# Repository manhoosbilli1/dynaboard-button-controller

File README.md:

# DynaButton

Dynaboard - STM32F103 multi-button HID/control interface with USB-C and high-density I/O

## At a Glance

- **Status**: Routed
- **Board size**: 48.31 x 52.88 mm
- **Layers**: 4
- **Components**: 68
- **Key ICs**:
  - U1: STM32F103C8T6
  - U2: U_REG LD1117S50TR_SOT223
  - U3: AMS1117
  - U4: 74LVC2G241

## Schematic

Full PDF: [reports/schematic.pdf](reports/schematic.pdf)

## Component Roles

- **STM32F103C8T6** (U1) - main MCU (ARM Cortex-M3, 72 MHz); handles button matrix scanning and USB HID
- **74LVC2G241** (U4) - dual buffer/line driver for clean digital I/O signaling on the button outputs
- **LD1117S50TR** (U2) - 5 V LDO for peripheral rail
- **AMS1117** (U3) - 3.3 V LDO for the STM32 core
- **BSS138** x3 (Q1-Q3) - small-signal N-MOSFETs for level shifting / open-drain signaling between 3.3 V MCU and 5 V peripherals
- **X50328MSB2GI** - 8 MHz crystal for STM32 system clock
- **USB-Type-C 16-pin** connector for power + data
- **SS33 Schottky** x2 (D1, D3) - reverse-polarity protection / freewheel diodes
- **JST-PH 2 mm** connectors for daisy-chained external buttons (J_BTN5-J_BTN8) and pass-through I/O (J_IN2, J_OUT2)

## PCB

**Top copper**

**Bottom copper**

## Bill of Materials

| Refs | Value | Footprint | Qty | MPN | LCSC |
|------|-------|-----------|----:|-----|------|
| C1,C13 | 10uF | PCM_JLCPCB:C_0402 | 2 |  | [C15525](https://www.lcsc.com/product-detail/_C15525.html) |
| C2-C7,C9-C11,C14 | 100nF | PCM_JLCPCB:C_0402 | 10 |  | [C1525](https://www.lcsc.com/product-detail/_C1525.html) |
| C8,C12,C15 | 1uF | PCM_JLCPCB:C_0402 | 3 |  | [C52923](https://www.lcsc.com/product-detail/_C52923.html) |
| C17,C18 | 20pF | PCM_JLCPCB:C_0402 | 2 |  | [C1554](https://www.lcsc.com/product-detail/_C1554.html) |
| C19,C20 | 12pF | PCM_JLCPCB:C_0402 | 2 |  | [C1547](https://www.lcsc.com/product-detail/_C1547.html) |
| D1,D3 | SS33 | PCM_JLCPCB:D_SMA | 2 |  | [C28646294](https://www.lcsc.com/product-detail/_C28646294.html) |
| D2 | Red | PCM_JLCPCB:D_0603 | 1 |  | [C2286](https://www.lcsc.com/product-detail/_C2286.html) |
| D4 | Yellow | PCM_JLCPCB:D_0603 | 1 |  | [C89811](https://www.lcsc.com/product-detail/_C89811.html) |
| J3,J4 | Conn_02x03_Odd_Even | Connector_PinHeader_2.54mm:PinHeader_2x03_P2.54mm_Vertical | 2 |  |  |
| J5 | Connector, USB-TYPE-C-16P | PCM_JLCPCB:TYPE-C-SMD_HX-TYPE-C-16PIN | 1 |  | [C2927039](https://www.lcsc.com/product-detail/_C2927039.html) |
| J_BTN5-J_BTN8 | JST PH 2-pin 2mm | Connector_JST:JST_PH_S2B-PH-SM4-TB_1x02-1MP_P2.00mm_Horizontal | 4 |  |  |
| J_IN2,J_OUT2 | JST PH 3-pin 2mm | Connector_JST:JST_PH_B3B-PH-SM4-TB_1x03-1MP_P2.00mm_Vertical | 2 |  |  |
| Q1-Q3 | BSS138 | PCM_JLCPCB:Q_SOT-23 | 3 |  | [C7420339](https://www.lcsc.com/product-detail/_C7420339.html) |
| R1,R9-R11,R16-R21 | 10kΩ | PCM_JLCPCB:R_0402 | 10 |  | [C25744](https://www.lcsc.com/product-detail/_C25744.html) |
| R2,R5 | 5.1kΩ | PCM_JLCPCB:R_0402 | 2 |  | [C25905](https://www.lcsc.com/product-detail/_C25905.html) |
| R3 | 1MΩ | PCM_JLCPCB:R_0402 | 1 |  | [C26083](https://www.lcsc.com/product-detail/_C26083.html) |
| R4,R22 | 330Ω | PCM_JLCPCB:R_0402 | 2 |  | [C25104](https://www.lcsc.com/product-detail/_C25104.html) |
| R6,R7 | 100kΩ | PCM_JLCPCB:R_0402 | 2 |  | [C25741](https://www.lcsc.com/product-detail/_C25741.html) |
| R8,R23 | 20Ω | PCM_JLCPCB:R_0603 | 2 |  | [C22950](https://www.lcsc.com/product-detail/_C22950.html) |
| R14 | 4.7kΩ | PCM_JLCPCB:R_0402 | 1 |  | [C25900](https://www.lcsc.com/product-detail/_C25900.html) |
| S1 | Tactile Button, 160gf | PCM_JLCPCB:SW_TS-1088-AR02016 | 1 |  | [C720477](https://www.lcsc.com/product-detail/_C720477.html) |
| U1 | STM32F103C8T6 | PCM_JLCPCB:LQFP-48_7x7mm_P0.5mm | 1 |  | [C8734](https://www.lcsc.com/product-detail/_C8734.html) |
| U2 | U_REG LD1117S50TR_SOT223 | Package_TO_SOT_SMD:SOT-223-3_TabPin2 | 1 |  |  |
| U3 | AMS1117 | PCM_JLCPCB:SOT-223-3_L6.5-W3.4-P2.30-LS7.0-BR | 1 |  | [C6186](https://www.lcsc.com/product-detail/_C6186.html) |
| U4 | 74LVC2G241 | Package_SO:VSSOP-8_3x3mm_P0.65mm | 1 |  |  |
| X2 | X50328MSB2GI | PCM_JLCPCB:CRYSTAL-SMD_L5.0-W3.2 | 1 |  | [C115962](https://www.lcsc.com/product-detail/_C115962.html) |
| X3 | Q13FC1350000400 | PCM_JLCPCB:FC-135R_L3.2-W1.5 | 1 |  | [C32346](https://www.lcsc.com/product-detail/_C32346.html) |

_5 of 27 line items don't have an LCSC code in the schematic - search [LCSC](https://www.lcsc.com/) or [JLC parts search](https://jlcsearch.tscircuit.com/) by MPN or footprint when sourcing._

## Files

- `DynaButton.kicad_pro` - KiCad project
- `DynaButton.kicad_sch` - schematic source
- `DynaButton.kicad_pcb` - PCB layout source
- `reports/schematic.pdf` - full schematic (printable)
- `reports/bom.csv` - bill of materials
- `reports/pcb-top.svg`, `reports/pcb-bottom.svg` - copper artwork
- `reports/board-stats.json` - KiCad-generated board statistics

---

_Renders and metadata auto-generated by `Backup-KiCadProject.ps1` using KiCad 10.0._

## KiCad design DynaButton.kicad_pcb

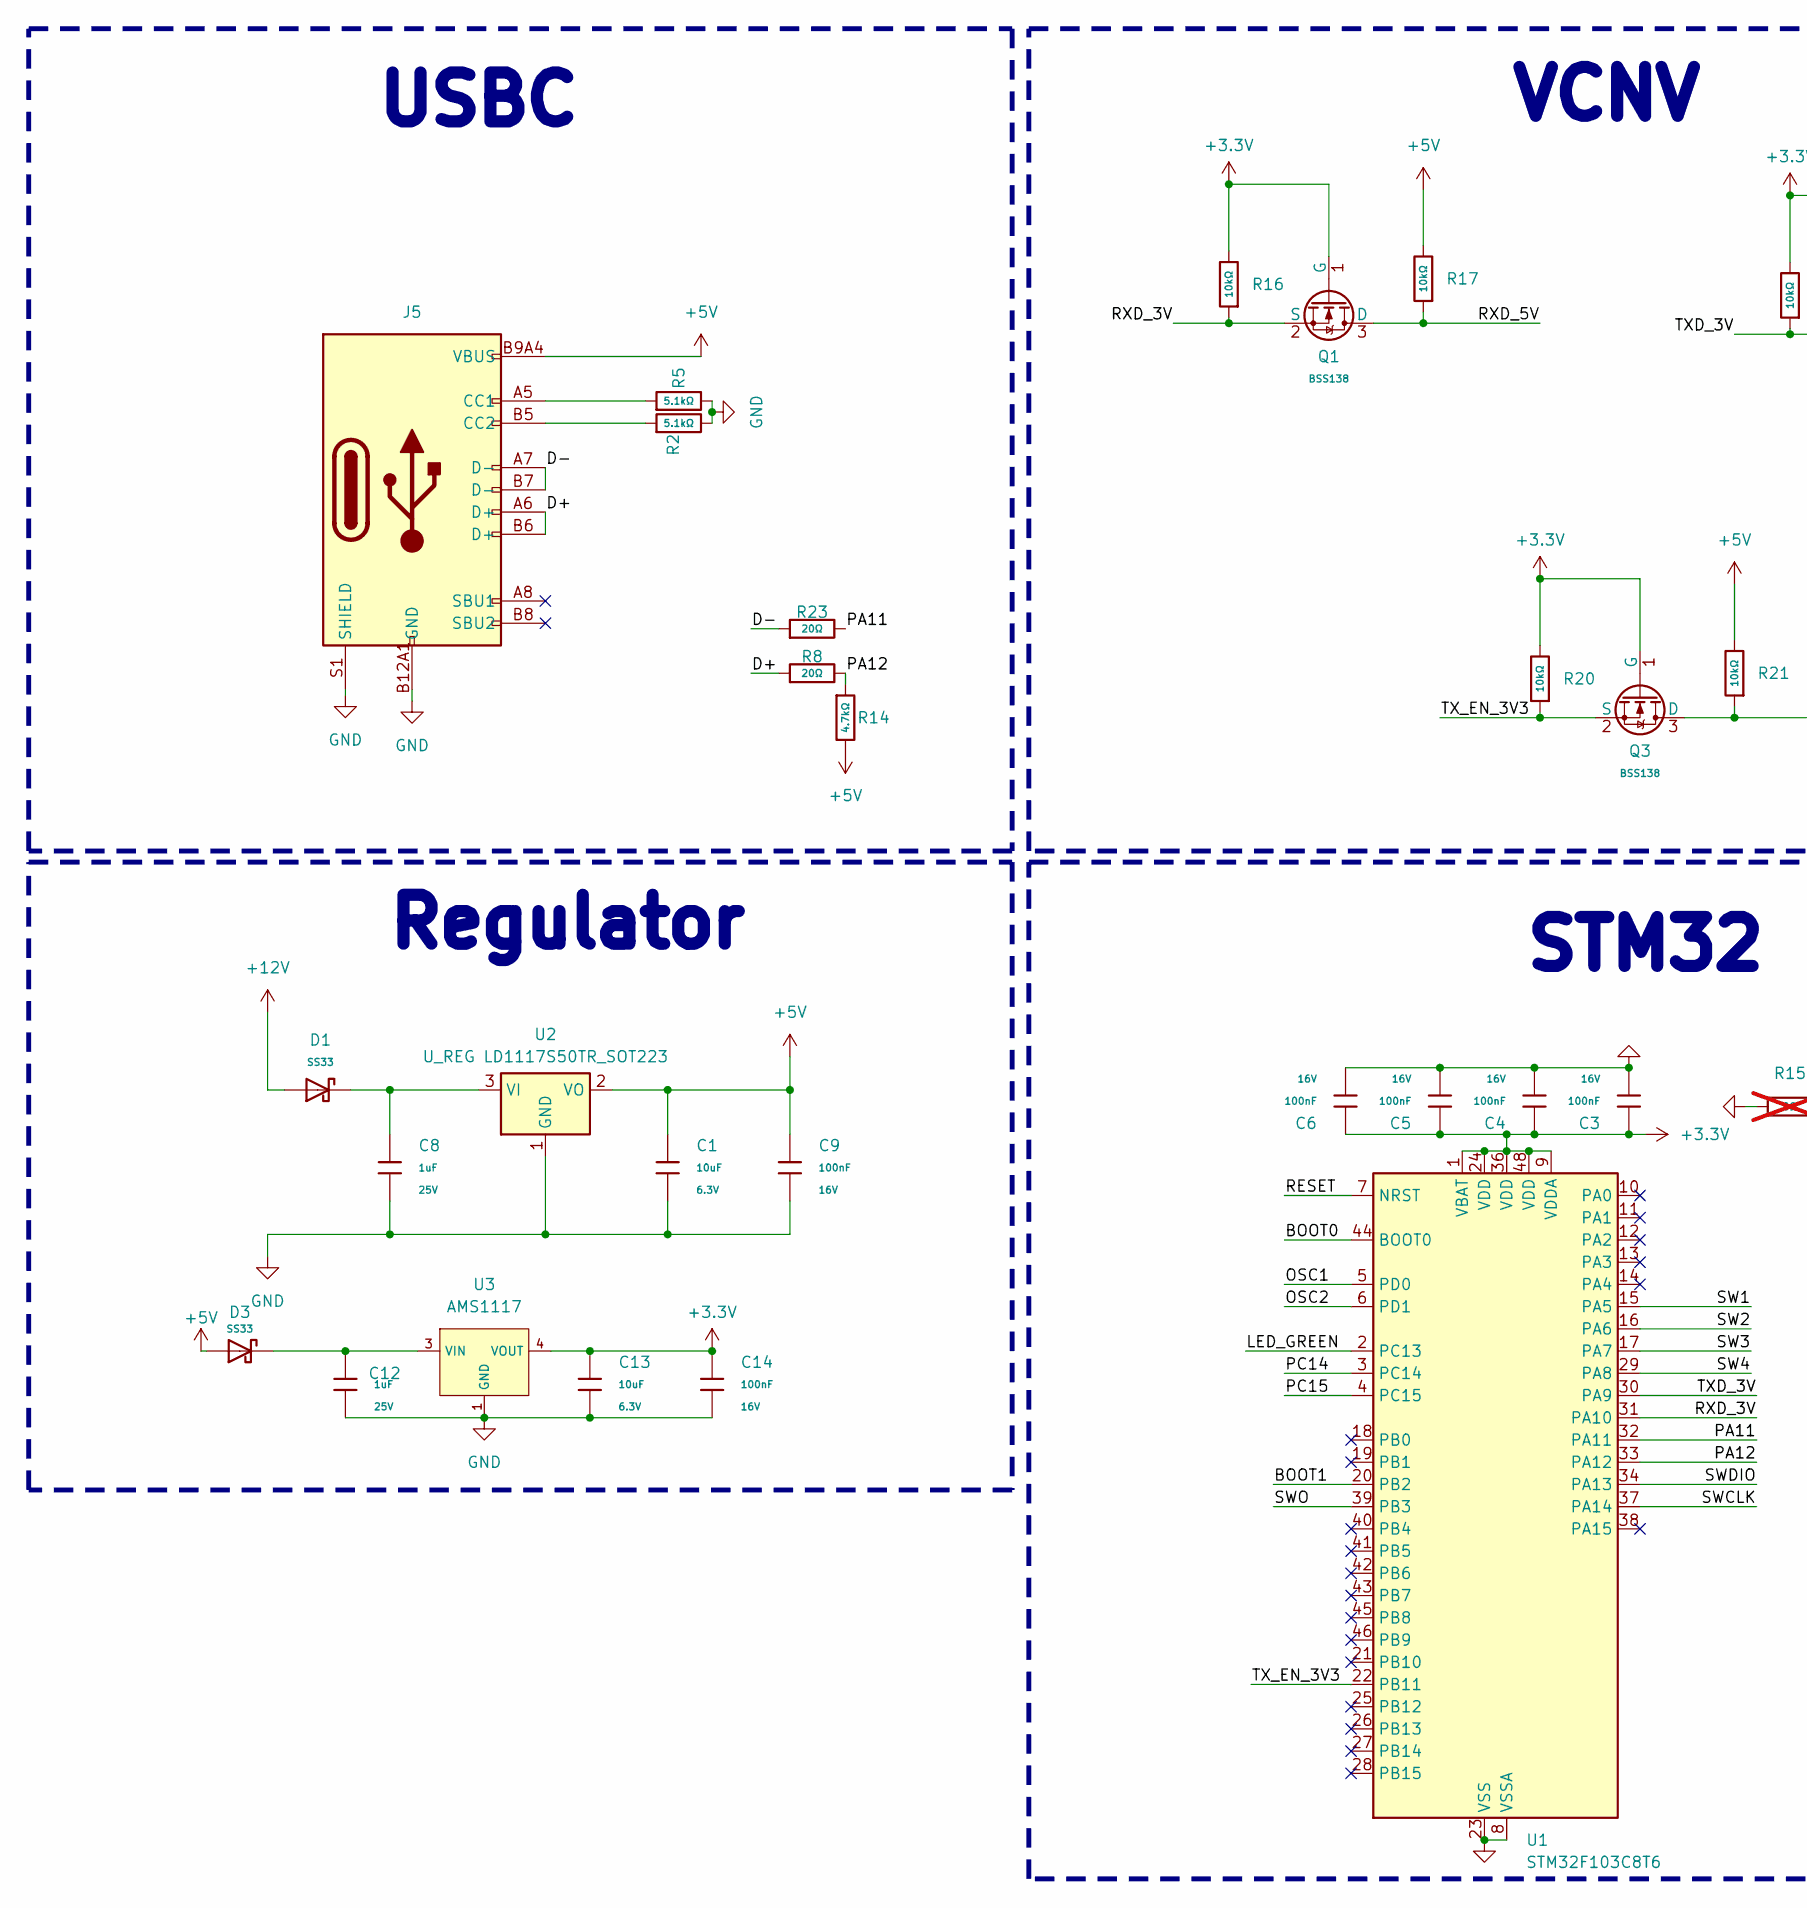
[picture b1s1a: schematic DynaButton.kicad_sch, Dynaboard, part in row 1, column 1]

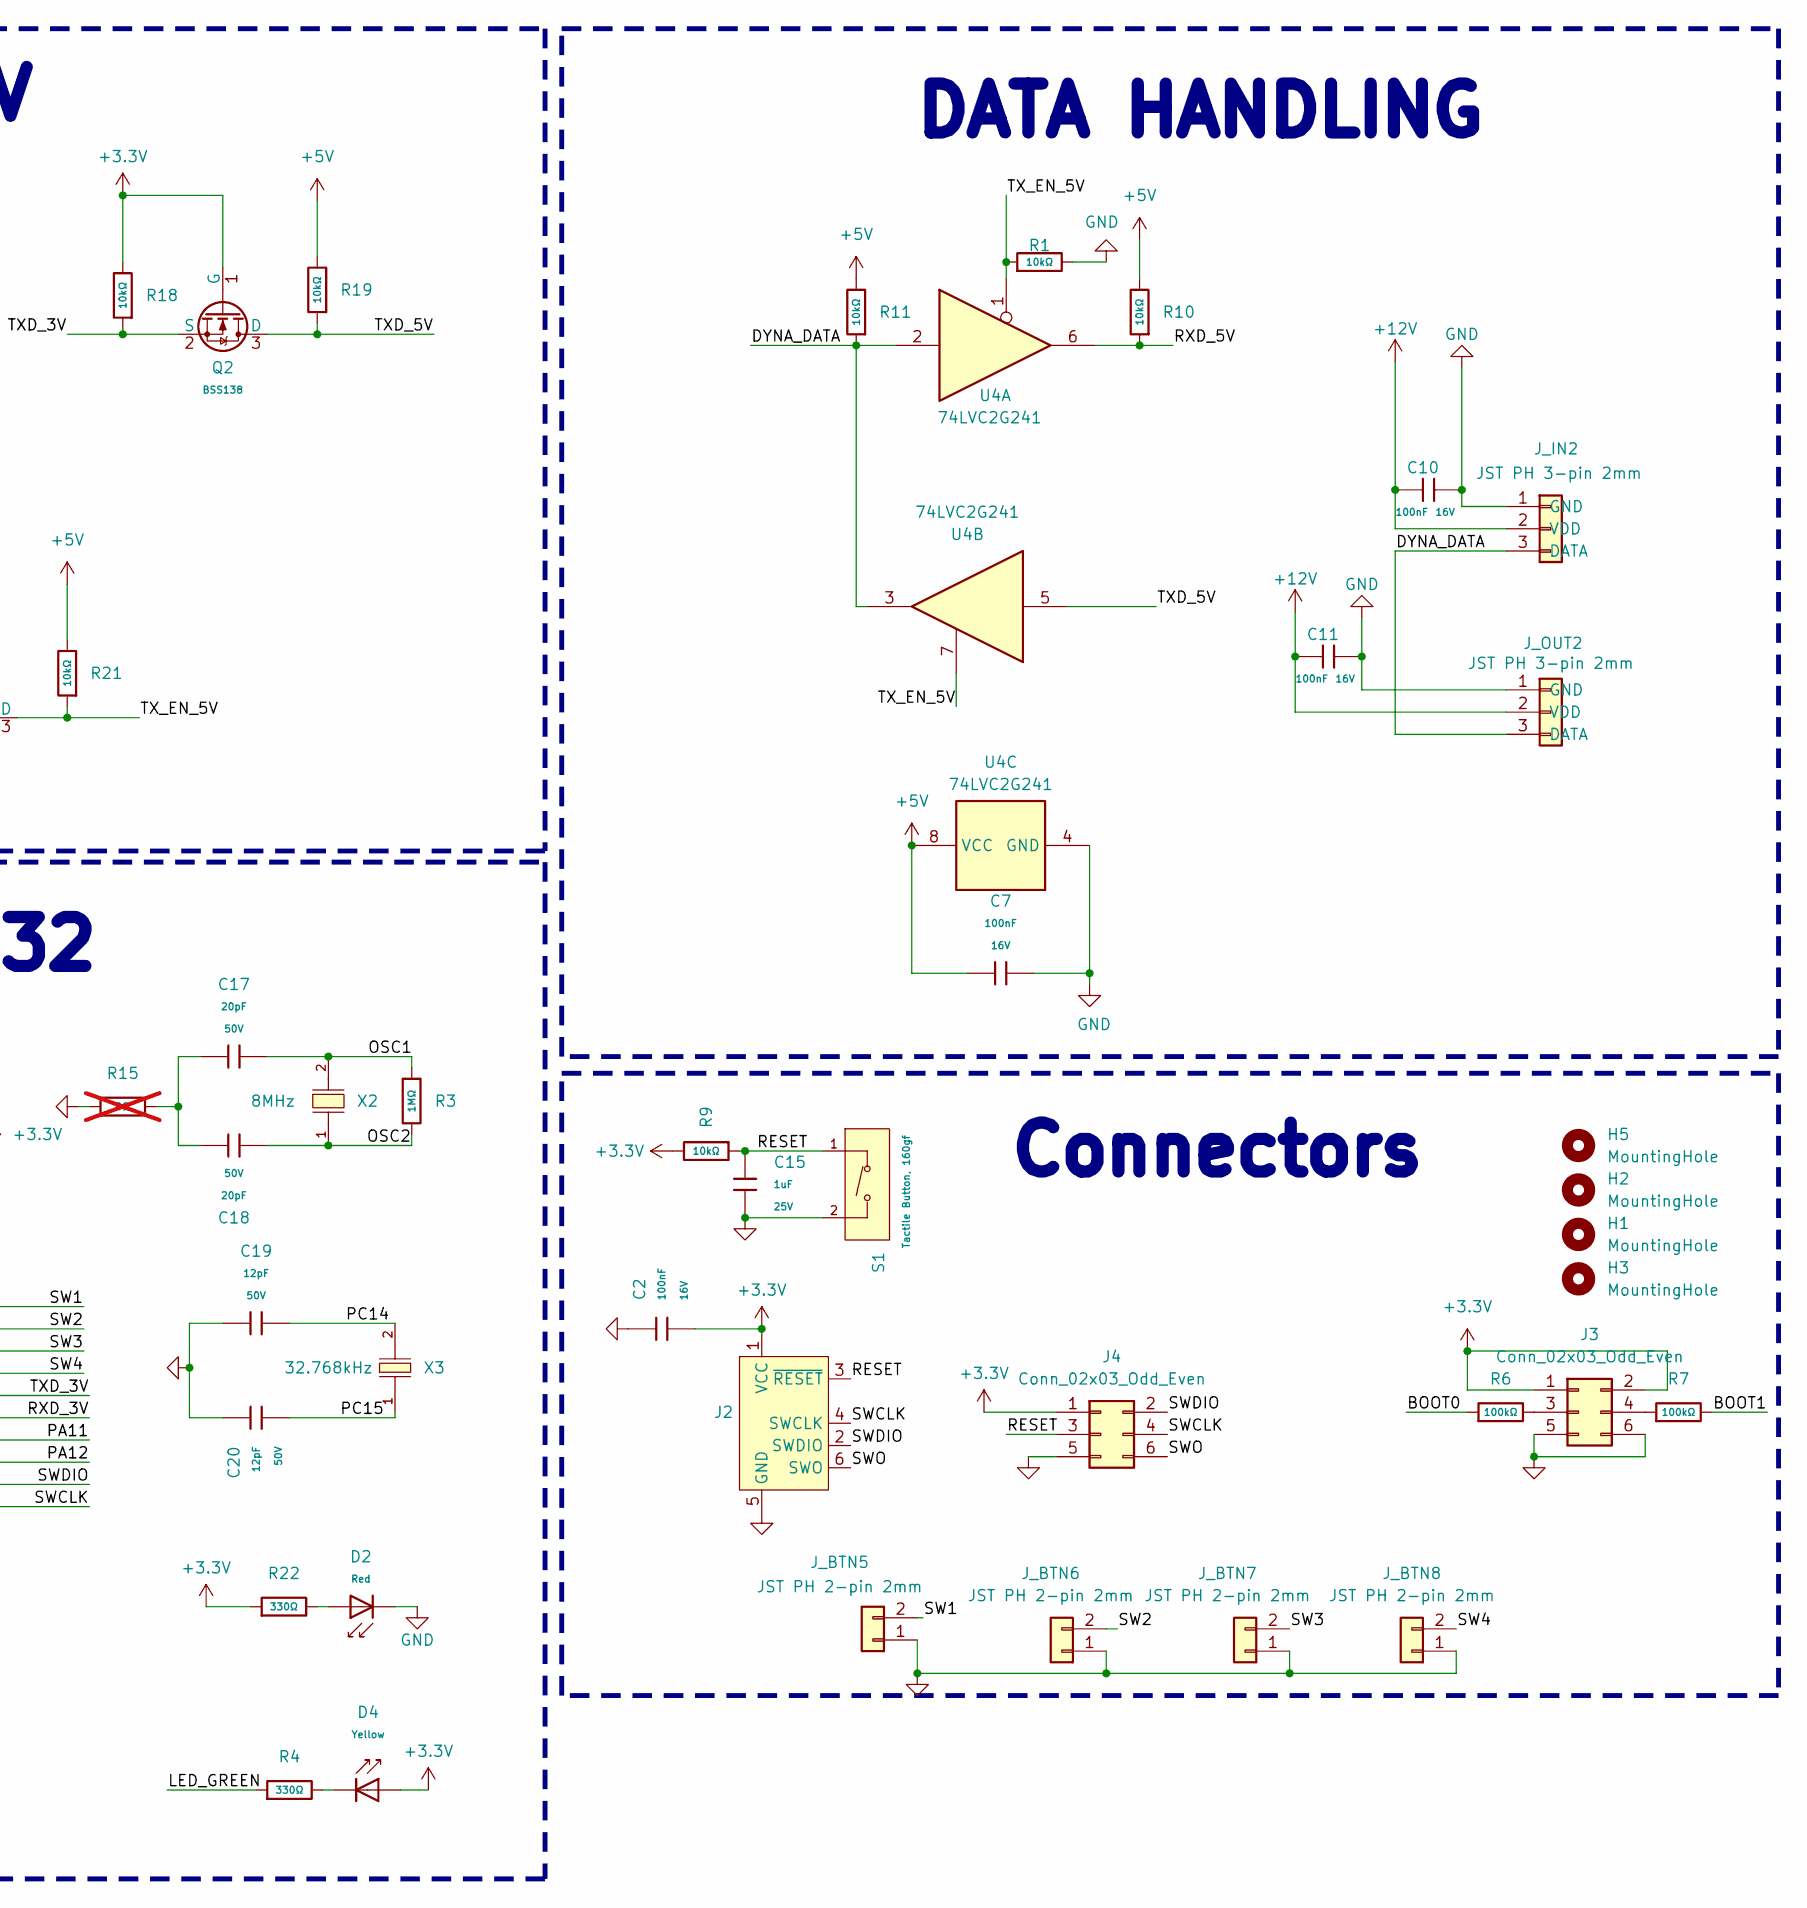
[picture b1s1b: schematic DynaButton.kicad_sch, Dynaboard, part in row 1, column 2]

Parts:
C1, C13: 10uF; C_0402; Voltage Rated 6.3V; Tolerance ±20%; Part CL05A106MQ5NUNC; LCSC C15525
C2, C3, C4, C5, C6, C7, C9, C10, C11, C14: 100nF; C_0402; Voltage Rated 16V; Tolerance ±10%; Part CL05B104KO5NNNC; LCSC C1525
C8, C12, C15: 1uF; C_0402; Voltage Rated 25V; Tolerance ±10%; Part CL05A105KA5NQNC; LCSC C52923
C17, C18: 20pF; C_0402; Voltage Rated 50V; Tolerance ±5%; Part 0402CG200J500NT; LCSC C1554
C19, C20: 12pF; C_0402; Voltage Rated 50V; Tolerance ±5%; Part 0402CG120J500NT; LCSC C1547
D1, D3: SS33; D_SMA; Part SS33; LCSC C28646294
D2: Red; D_0603; Part KT-0603R; LCSC C2286
D4: Yellow; D_0603; Forward Voltage (VF) 1.6V~2.6V; Part NCD0603Y2; LCSC C89811
H1, H2, H3, H5: MountingHole; MountingHole_2.2mm_M2
J2: Conn_ARM_SWD_TagConnect_TC2030; Tag-Connect_TC2030-IDC-FP_2x03_P1.27mm_Vertical
J3, J4: Conn_02x03_Odd_Even; PinHeader_2x03_P2.54mm_Vertical
J5: Connector, USB-TYPE-C-16P; TYPE-C-SMD_HX-TYPE-C-16PIN; LCSC C2927039
J_BTN5, J_BTN6, J_BTN7, J_BTN8: JST PH 2-pin 2mm; JST_PH_S2B-PH-SM4-TB_1x02-1MP_P2.00mm_Horizontal; PART NUMBER C295747
J_IN2: JST PH 3-pin 2mm; JST_PH_B3B-PH-SM4-TB_1x03-1MP_P2.00mm_Vertical; JLCPCB PART # C160353
J_OUT2: JST PH 3-pin 2mm; JST_PH_B3B-PH-SM4-TB_1x03-1MP_P2.00mm_Vertical; JLCPCB PART # C160353
Q1, Q2, Q3: BSS138; Q_SOT-23; Part BSS138; LCSC C7420339
R1, R9, R10, R11, R16, R17, R18, R19, R20, R21: 10kΩ; R_0402; Overload Voltage (Max) 50V; Tolerance ±1%; Part 0402WGF1002TCE; LCSC C25744
R2, R5: 5.1kΩ; R_0402; Overload Voltage (Max) 50V; Tolerance ±1%; Part 0402WGF5101TCE; LCSC C25905
R3: 1MΩ; R_0402; Overload Voltage (Max) 50V; Tolerance ±1%; Part 0402WGF1004TCE; LCSC C26083
R4, R22: 330Ω; R_0402; Overload Voltage (Max) 50V; Tolerance ±1%; Part 0402WGF3300TCE; LCSC C25104
R6, R7: 100kΩ; R_0402; Overload Voltage (Max) 50V; Tolerance ±1%; Part 0402WGF1003TCE; LCSC C25741
R8, R23: 20Ω; R_0603; Overload Voltage (Max) 75V; Tolerance ±1%; Part 0603WAF200JT5E; LCSC C22950
R14: 4.7kΩ; R_0402; Overload Voltage (Max) 50V; Tolerance ±1%; Part 0402WGF4701TCE; LCSC C25900
R15: 0Ω; R_0402; Overload Voltage (Max) 50V; Tolerance ±1%; Part 0402WGF0000TCE; LCSC C17168; not fitted
S1: Tactile Button, 160gf; SW_TS-1088-AR02016; Voltage Rating (Dc) 12V; Part TS-1088-AR02016; LCSC C720477
U1: STM32F103C8T6; LQFP-48_7x7mm_P0.5mm; Operating Voltage Range 2V~3.6V; Low Voltage Detection T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 2V~3.6V; Part STM32F103C8T6; LCSC C8734
U2: U_REG LD1117S50TR_SOT223; SOT-223-3_TabPin2; PART NUMBER C134077
U3: AMS1117; SOT-223-3_L6.5-W3.4-P2.30-LS7.0-BR; Output Voltage 3.3V; Dropout Voltage 1.3V@(800mA); Part AMS1117-3.3; LCSC C6186
U4: 74LVC2G241; VSSOP-8_3x3mm_P0.65mm
X2: X50328MSB2GI; CRYSTAL-SMD_L5.0-W3.2; Frequency Tolerance ±10ppm; Part X50328MSB2GI; LCSC C115962
X3: Q13FC1350000400; FC-135R_L3.2-W1.5; Frequency Tolerance ±20ppm; Part Q13FC13500004; LCSC C32346

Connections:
+3.3V: C2.2, C3.1, C4.1, C5.1, C6.1, C13.1, C14.1, D4.2, J2.1 (VCC), J3.1, J3.2, J4.1, Q1.1 (G), Q2.1 (G), Q3.1 (G), R9.2, R16.2, R18.2, R20.2, R22.1, U1.1 (VBAT), U1.9 (VDDA), U1.24 (VDD), U1.36 (VDD), U1.48 (VDD), U3.2 (VOUT), U3.4 (VOUT)
+5V: C1.1, C7.1, C9.1, D3.2, J5.A9B4 (VBUS), J5.B9A4 (VBUS), R10.2, R11.2, R14.2, R17.2, R19.2, R21.2, U2.2 (VO), U4.8 (VCC)
+12V: C10.2, C11.2, D1.2, J_IN2.2 (VDD), J_OUT2.2 (VDD)
/BOOT0: R6.1, U1.44 (BOOT0)
/BOOT1: R7.2, U1.20 (PB2)
/D+: J5.A6 (D+), J5.B6 (D+), R8.1
/D-: J5.A7 (D-), J5.B7 (D-), R23.1
/DYNA_DATA: J_IN2.3 (DATA), J_OUT2.3 (DATA), R11.1, U4.2, U4.3
/LED_GREEN: R4.1, U1.2 (PC13)
/OSC1: C17.2, R3.1, U1.5 (PD0), X2.2
/OSC2: C18.2, R3.2, U1.6 (PD1), X2.1
/PA11: R23.2, U1.32 (PA11)
/PA12: R8.2, R14.1, U1.33 (PA12)
/PC14: C19.2, U1.3 (PC14), X3.2
/PC15: C20.1, U1.4 (PC15), X3.1
/RESET: C15.1, J2.3 (~RESET), J4.3, R9.1, S1.1 (A), U1.7 (NRST)
/RXD_3V: Q1.2 (S), R16.1, U1.31 (PA10)
/RXD_5V: Q1.3 (D), R10.1, R17.1, U4.6
/SW1: J_BTN5.2, U1.15 (PA5)
/SW2: J_BTN6.2, U1.16 (PA6)
/SW3: J_BTN7.2, U1.17 (PA7)
/SW4: J_BTN8.2, U1.29 (PA8)
/SWCLK: J2.4 (SWCLK), J4.4, U1.37 (PA14)
/SWDIO: J2.2 (SWDIO), J4.2, U1.34 (PA13)
/SWO: J2.6 (SWO), J4.6, U1.39 (PB3)
/TXD_3V: Q2.2 (S), R18.1, U1.30 (PA9)
/TXD_5V: Q2.3 (D), R19.1, U4.5
/TX_EN_3V3: Q3.2 (S), R20.1, U1.22 (PB11)
/TX_EN_5V: Q3.3 (D), R1.1, R21.1, U4.1, U4.7
GND: C1.2, C2.1, C3.2, C4.2, C5.2, C6.2, C7.2, C8.2, C9.2, C10.1, C11.1, C12.2, C13.2, C14.2, C15.2, C19.1, C20.2, D2.1, J2.5 (GND), J3.5, J3.6, J4.5, J5.A12B1 (GND), J5.B12A1 (GND), J5.S1 (SHIELD), J_BTN5.1, J_BTN6.1, J_BTN7.1, J_BTN8.1, J_IN2.1 (GND), J_OUT2.1 (GND), R1.2, R2.2, R5.2, R15.1, S1.2 (B), U1.8 (VSSA), U1.23 (VSS), U1.35 (VSS), U1.47 (VSS), U2.1 (GND), U3.1 (GND), U4.4 (GND)
unnamed: C17.1, C18.1, R15.2
unnamed: D2.2, R22.2
unnamed: D4.1, R4.2
unnamed: J3.3, R6.2
unnamed: J3.4, R7.1
unnamed: J5.A5 (CC1), R5.1
unnamed: J5.B5 (CC2), R2.1
unnamed: C8.1, D1.1, U2.3 (VI)
unnamed: C12.1, D3.1, U3.3 (VIN)

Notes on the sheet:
Regulator
DATA HANDLING
USBC
STM32
Connectors
VCNV

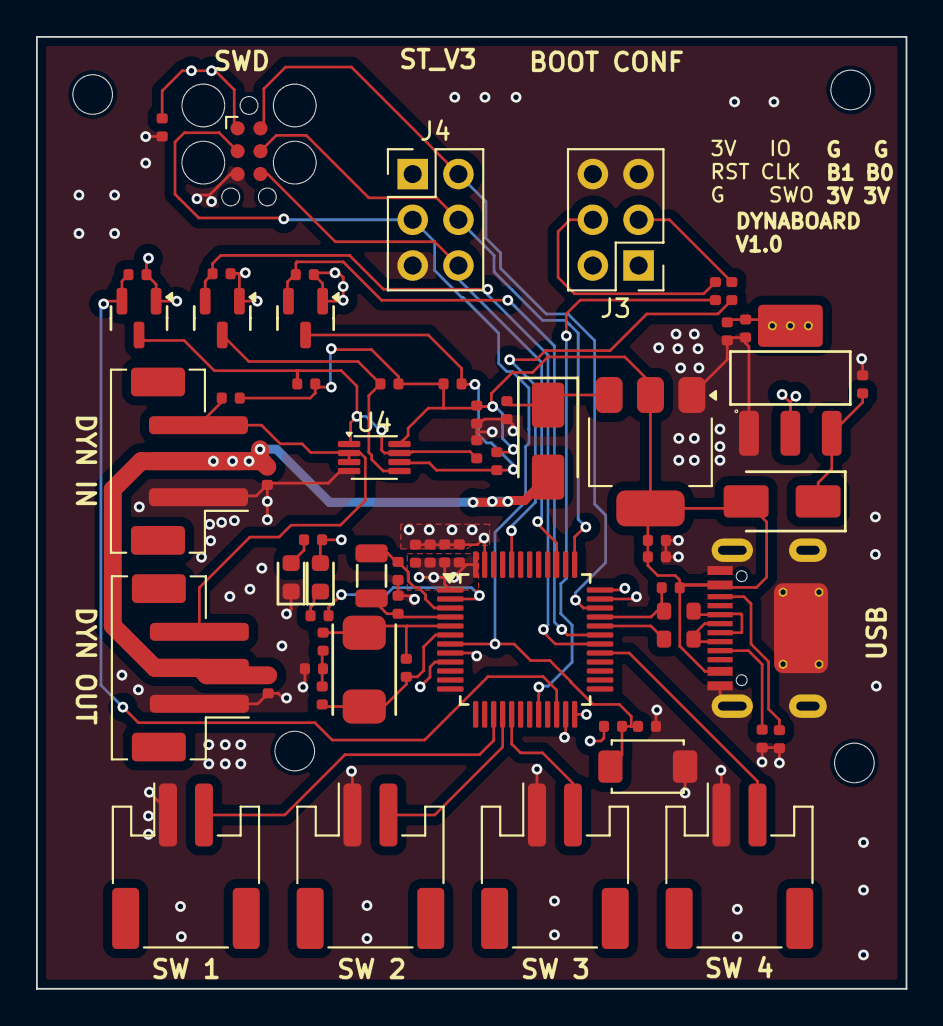
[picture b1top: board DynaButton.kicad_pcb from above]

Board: 4 copper layers, 48.3 x 52.9 mm, 68 parts (0 on the bottom side), 39 nets.

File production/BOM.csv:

Designator,Footprint,Quantity,Value,LCSC Part #
"C1, C13",C_0402,2,10uF,C15525
"C10, C11, C14, C2, C3, C4, C5, C6, C7, C9",C_0402,10,100nF,C1525
"C12, C15, C8",C_0402,3,1uF,C52923
"C17, C18",C_0402,2,20pF,C1554
"C19, C20",C_0402,2,12pF,C1547
"D1, D3",D_SMA,2,SS33,C28646294
D2,D_0603,1,Red,C2286
D4,D_0603,1,Yellow,C89811
"J3, J4",PinHeader_2x03_P2.54mm_Vertical,2,Conn_02x03_Odd_Even,
J5,TYPE-C-SMD_HX-TYPE-C-16PIN,1,"Connector, USB-TYPE-C-16P",C2927039
"J_BTN5, J_BTN6, J_BTN7, J_BTN8",JST_PH_S2B-PH-SM4-TB_1x02-1MP_P2.00mm_Horizontal,4,JST PH 2-pin 2mm,
"J_IN2, J_OUT2",JST_PH_B3B-PH-SM4-TB_1x03-1MP_P2.00mm_Vertical,2,JST PH 3-pin 2mm,
"Q1, Q2, Q3",Q_SOT-23,3,BSS138,C7420339
"R1, R10, R11, R16, R17, R18, R19, R20, R21, R9",R_0402,10,10kΩ,C25744
R14,R_0402,1,4.7kΩ,C25900
"R2, R5",R_0402,2,5.1kΩ,C25905
"R22, R4",R_0402,2,330Ω,C25104
"R23, R8",R_0603,2,20Ω,C22950
R3,R_0402,1,1MΩ,C26083
"R6, R7",R_0402,2,100kΩ,C25741
S1,SW_TS-1088-AR02016,1,"Tactile Button, 160gf",C720477
U1,LQFP-48_7x7mm_P0.5mm,1,STM32F103C8T6,C8734
U2,SOT-223-3_TabPin2,1,U_REG LD1117S50TR_SOT223,
U3,SOT-223-3_L6.5-W3.4-P2.30-LS7.0-BR,1,AMS1117,C6186
U4,VSSOP-8_2.3x2mm_P0.5mm,1,74LVC2G241,
X2,CRYSTAL-SMD_L5.0-W3.2,1,X50328MSB2GI,C115962
X3,FC-135R_L3.2-W1.5,1,Q13FC1350000400,C32346

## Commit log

2026-05-18 Update backup artifacts
2026-05-18 Enrich README: schematic PNG, component roles, BOM table
